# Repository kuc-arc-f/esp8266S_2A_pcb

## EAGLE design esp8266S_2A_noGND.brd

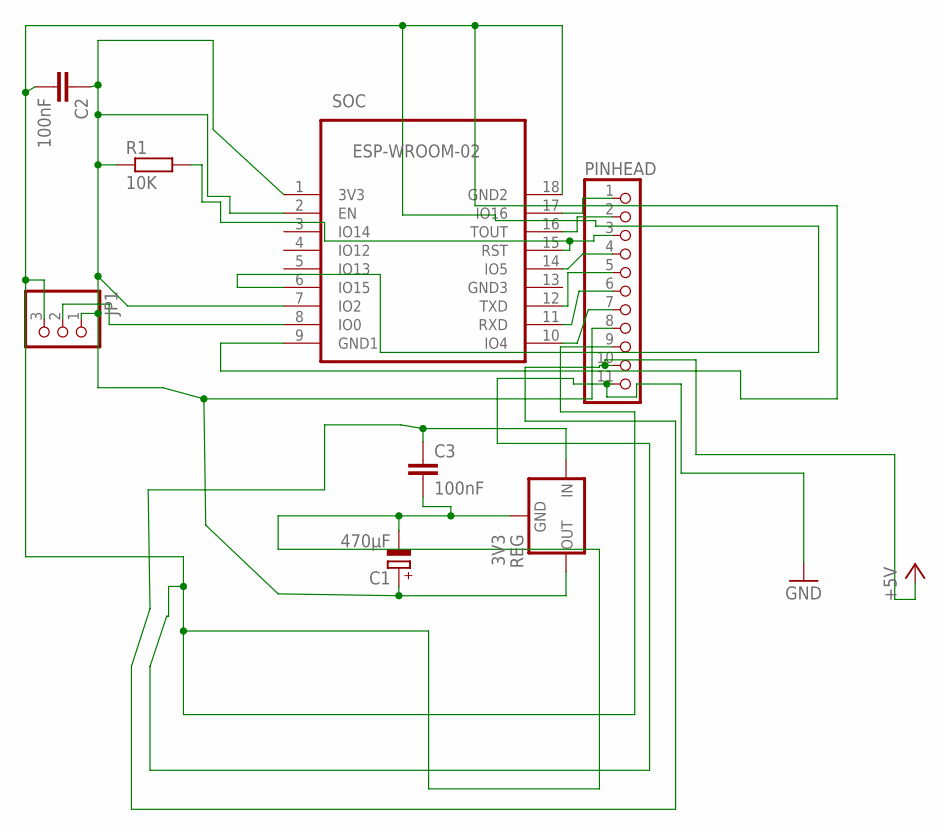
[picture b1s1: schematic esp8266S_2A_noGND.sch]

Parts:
C1: 470μF; E2,5-7
C2, C3: 100nF; C0603
JP1: PINHD-1X3; 1X03
PINHEAD: PINHD-1X11; 1X11
R1: 10K; R0603
REG: 3V3; 78XXS
SOC: ESP-WROOM-02; FRONT-FACE-CP2

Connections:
+5V: C3.1, PINHEAD.10, REG.IN
GND: C1.-, C2.2, C3.2, JP1.3, PINHEAD.9, PINHEAD.11, REG.GND, SOC.6 (IO15), SOC.9 (GND1), SOC.18 (GND2)
unnamed: JP1.2, SOC.8 (IO0)
unnamed: PINHEAD.1, SOC.17 (IO16)
unnamed: PINHEAD.2, SOC.16 (TOUT)
unnamed: PINHEAD.4, SOC.14 (IO5)
unnamed: PINHEAD.5, SOC.12 (TXD)
unnamed: PINHEAD.6, SOC.11 (RXD)
unnamed: PINHEAD.7, SOC.10 (IO4)
unnamed: C1.+, C2.1, JP1.1, PINHEAD.8, R1.1, REG.OUT, SOC.1 (3V3), SOC.2 (EN), SOC.7 (IO2)
unnamed: PINHEAD.3, R1.2, SOC.15 (RST)

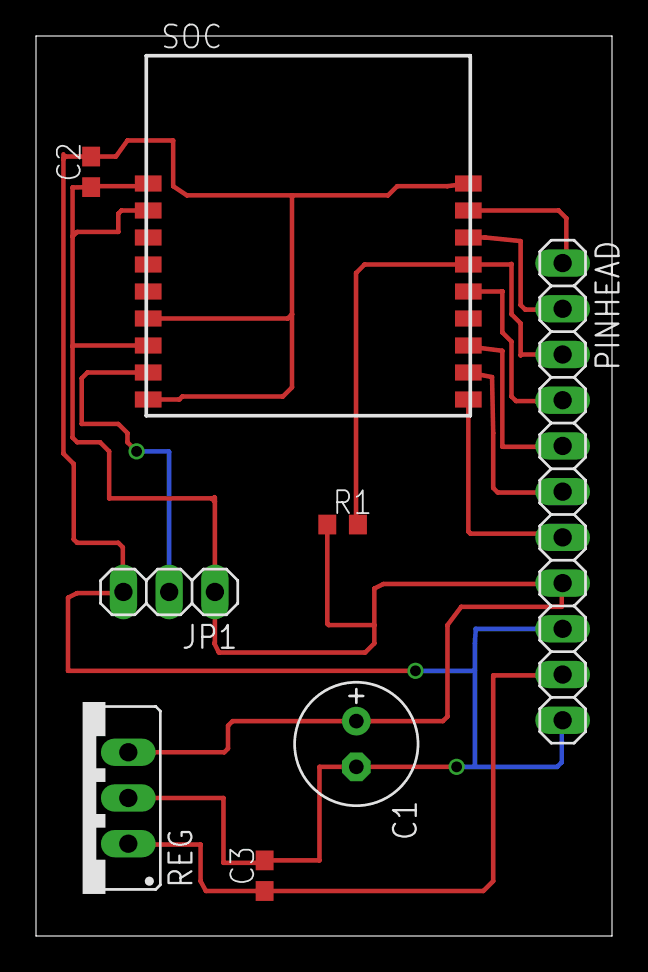
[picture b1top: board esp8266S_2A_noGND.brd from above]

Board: 2 copper layers, 32.0 x 50.0 mm, 8 parts (0 on the bottom side), 11 nets.

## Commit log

2016-09-27 new, 09-27A1
